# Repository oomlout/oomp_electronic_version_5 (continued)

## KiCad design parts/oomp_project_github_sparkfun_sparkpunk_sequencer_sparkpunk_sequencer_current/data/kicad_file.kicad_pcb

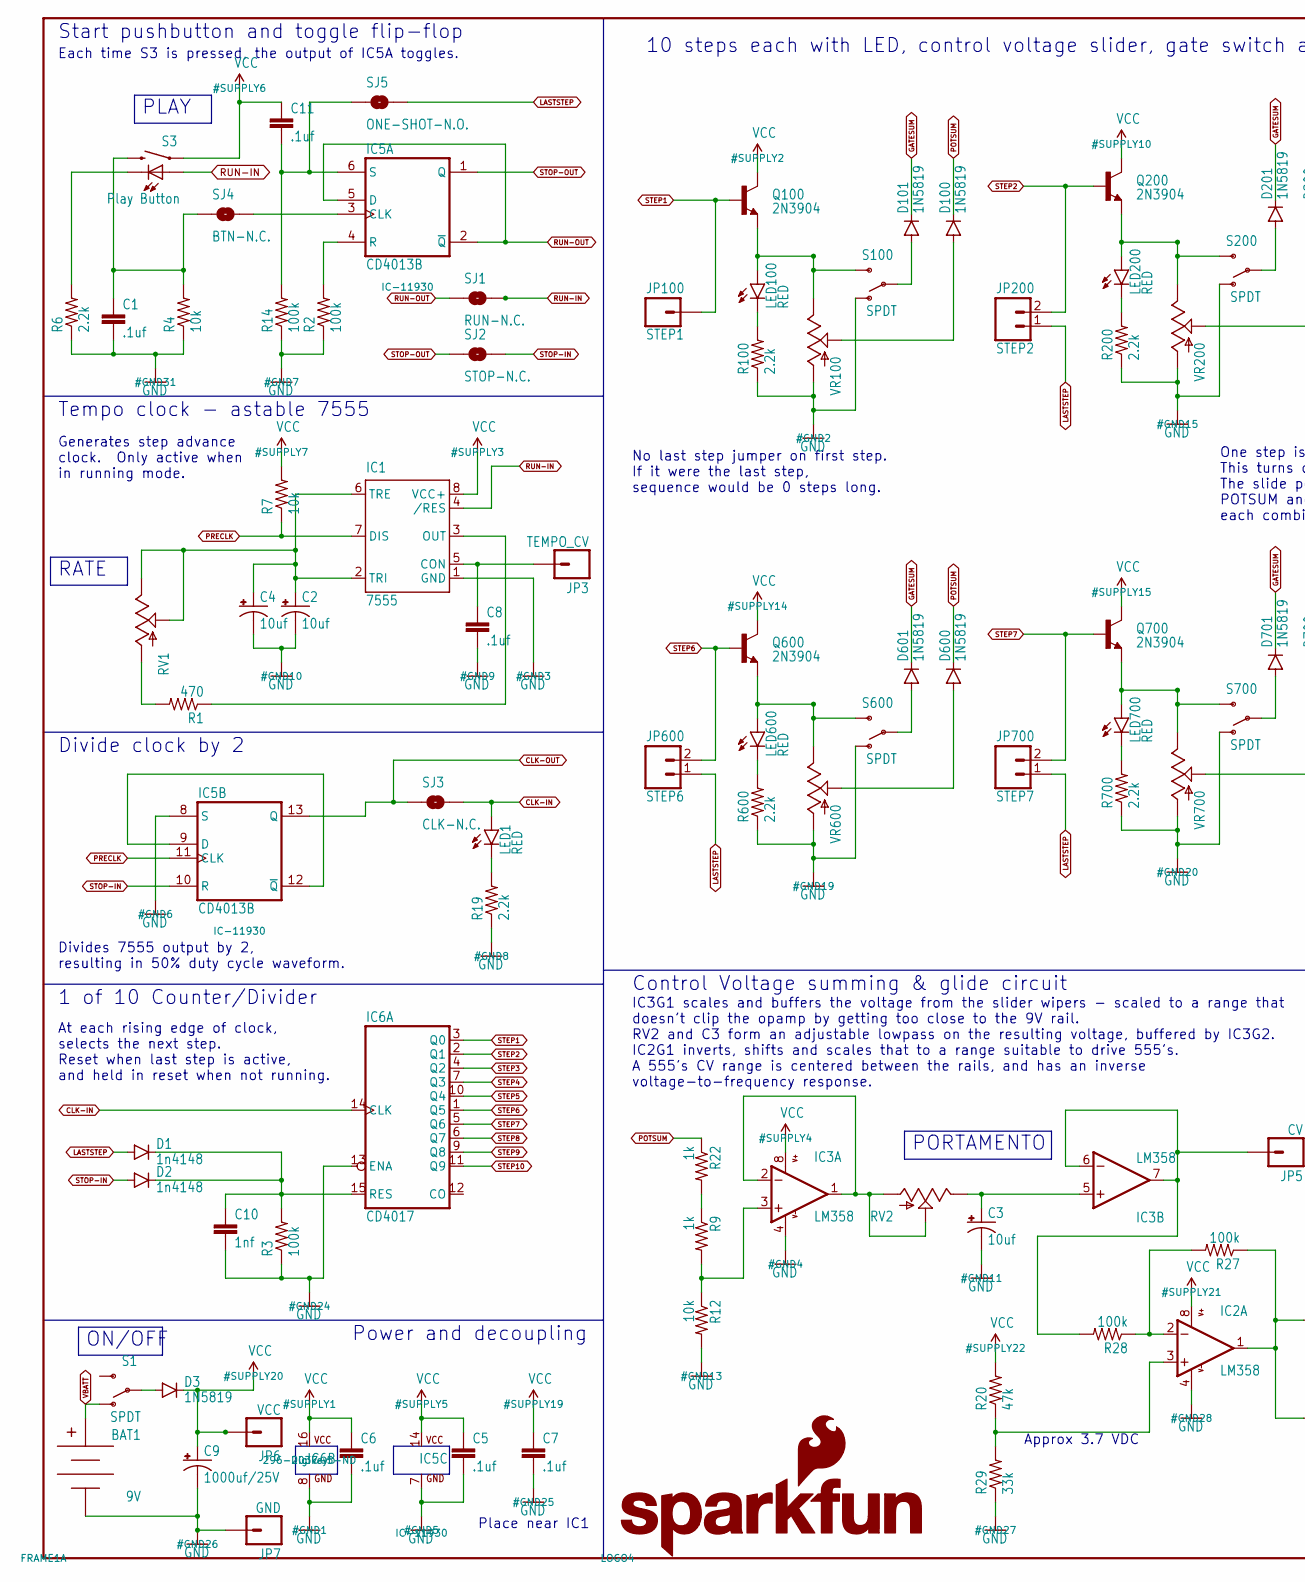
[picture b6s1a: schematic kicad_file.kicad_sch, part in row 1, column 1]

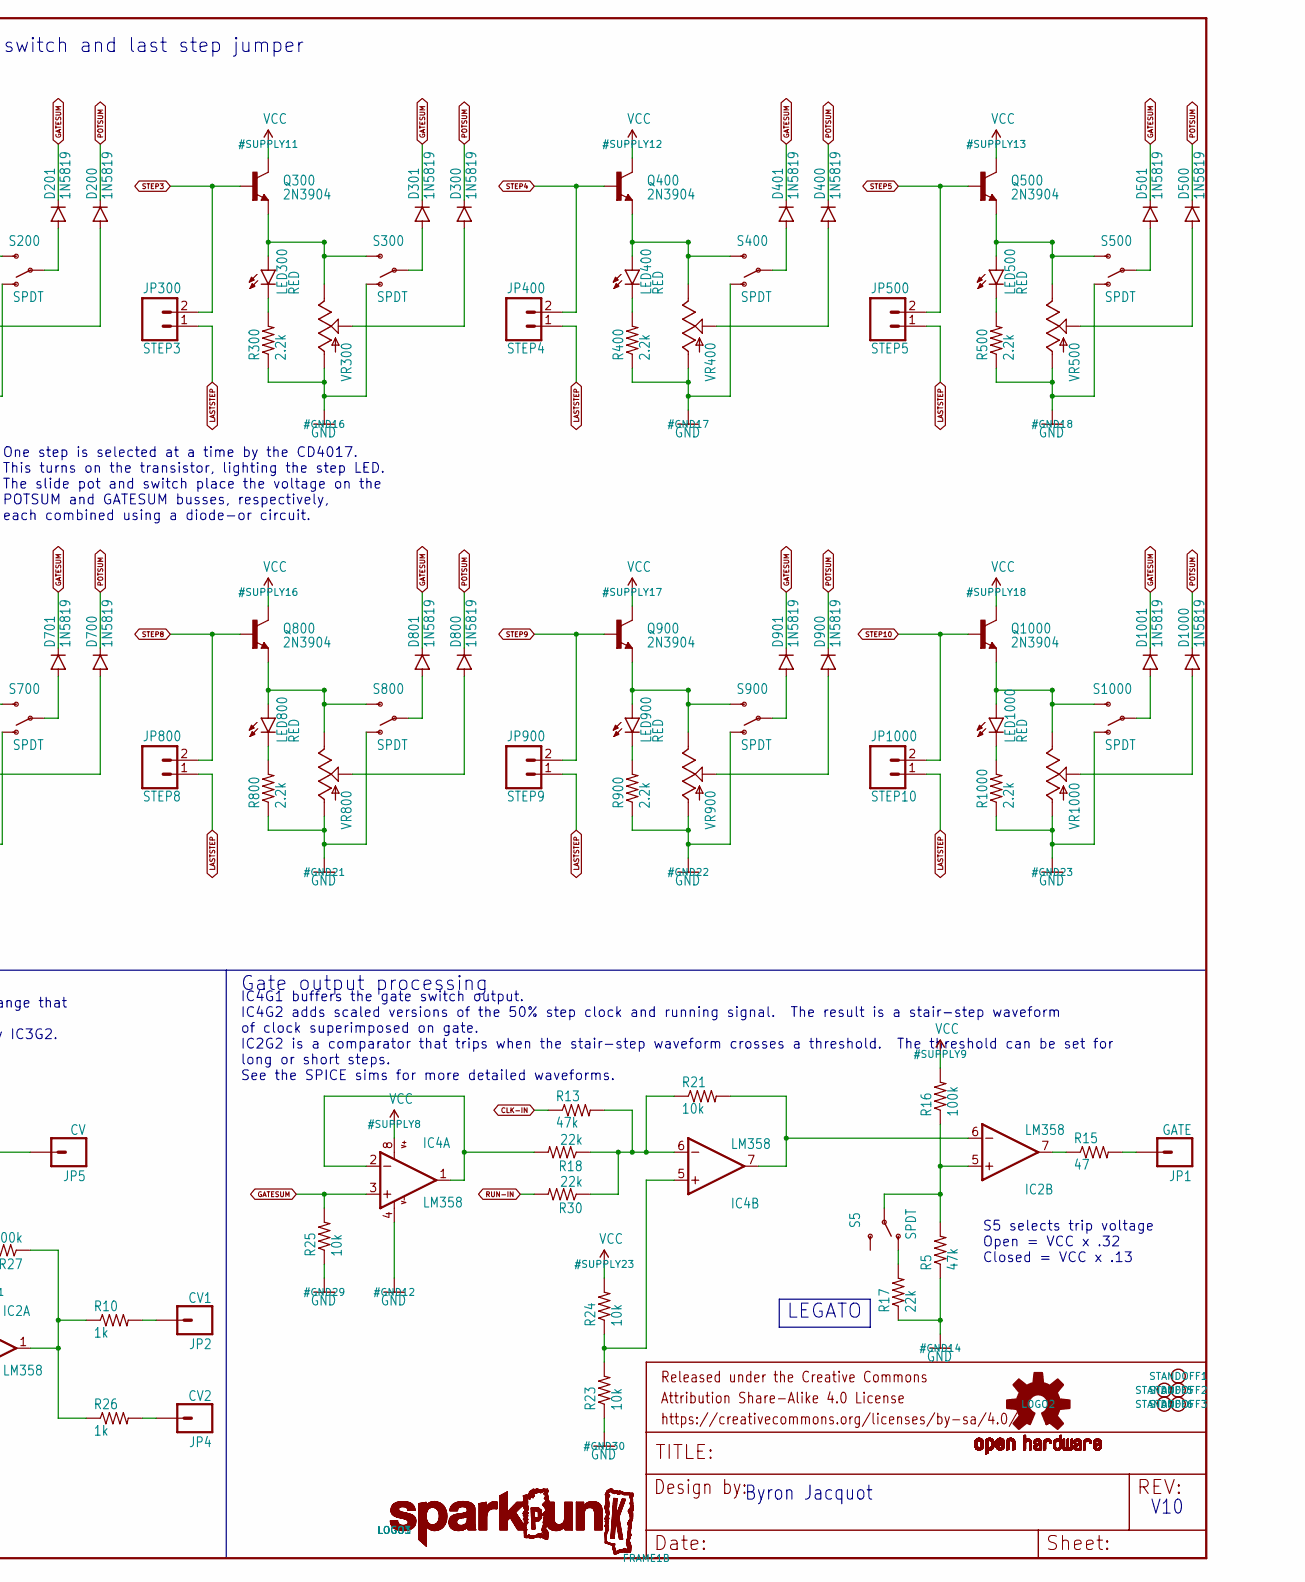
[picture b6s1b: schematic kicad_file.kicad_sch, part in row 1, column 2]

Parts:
BAT1: 9V; BC9VPC_KIT
C1, C5, C6, C7, C8, C11: .1uf; CAP-PTH-SMALL-KIT
C2, C3, C4: 10uf; CPOL-RADIAL-10UF-25V-KIT
C9: 1000uf/25V; CPOL-RADIAL-1000UF-25V-KIT
C10: 1nf; CAP-PTH-SMALL-KIT
D1, D2: 1n4148; DIODE-1N4148-KIT
D3, D100, D101, D200, D201, D300, D301, D400, D401, D500, D501, D600, D601, D700, D701, D800, D801, D900, D901, D1000, D1001: 1N5819; DIODE-1N4001-KIT
FRAME1: FRAME-LEDGER; CREATIVE_COMMONS
IC1: 7555; DIP08-KIT
IC2, IC3, IC4: LM358; DIP08-KIT
IC5: CD4013B; DIL14-KIT
IC6: CD4017; DIL16-KIT
JP1: GATE; 1X01NS
JP2: CV1; 1X01NS
JP3: TEMPO_CV; 1X01NS
JP4: CV2; 1X01NS
JP5: CV; 1X01NS
JP6: VCC; 1X01NS
JP7: GND; 1X01NS
JP100: STEP1; 1X01NS
JP200: STEP2; 1X02_NO_SILK
JP300: STEP3; 1X02_NO_SILK
JP400: STEP4; 1X02_NO_SILK
JP500: STEP5; 1X02_NO_SILK
JP600: STEP6; 1X02_NO_SILK
JP700: STEP7; 1X02_NO_SILK
JP800: STEP8; 1X02_NO_SILK
JP900: STEP9; 1X02_NO_SILK
JP1000: STEP10; 1X02_NO_SILK
LED1, LED100, LED200, LED300, LED400, LED500, LED600, LED700, LED800, LED900, LED1000: RED; LED5MM-KIT
LOGO1: SPARKPUNK_LOGO.2_INCH_TALL; SPARKPUNK_LOGO_.2
LOGO2: OSHW-LOGOM; OSHW-LOGO-M
LOGO3: SPARKPUNK_LOGO.1INCH_TALL; SPARKPUNK_LOGO_.1
LOGO4: SFE_LOGO_NAME_FLAME.4_INCH; SFE_LOGO_NAME_FLAME_.4
Q100, Q200, Q300, Q400, Q500, Q600, Q700, Q800, Q900, Q1000: 2N3904; TO-92-AMMO
R1: 470; AXIAL-0.3EZ
R2, R3, R14, R16, R27, R28: 100k; AXIAL-0.3EZ
R4, R7, R12, R21, R23, R24, R25: 10k; AXIAL-0.3EZ
R5, R13, R20: 47k; AXIAL-0.3EZ
R6, R19, R100, R200, R300, R400, R500, R600, R700, R800, R900, R1000: 2.2k; AXIAL-0.3EZ
R9, R10, R22, R26: 1k; AXIAL-0.3EZ
R15: 47; AXIAL-0.3EZ
R17, R18, R30: 22k; AXIAL-0.3EZ
R29: 33k; AXIAL-0.3EZ
RV1, RV2: 10k; ALPS_POT_KIT
S1, S5, S100, S200, S300, S400, S500, S600, S700, S800, S900, S1000: SPDT; SWITCH-SPDT_KIT
S3: Play Button; TACTILE-PTH-LED-12MM-EZ
SJ1: RUN-N.C.; SJ_2S-TRACE-PTH
SJ2: STOP-N.C.; SJ_2S-TRACE-PTH
SJ3: CLK-N.C.; SJ_2S-TRACE-PTH
SJ4: BTN-N.C.; SJ_2S-TRACE-PTH
SJ5: ONE-SHOT-N.O.; SJ_2S-PTH
STANDOFF1, STANDOFF2, STANDOFF3, STANDOFF5, STANDOFF6: STAND-OFF
VR100, VR200, VR300, VR400, VR500, VR600, VR700, VR800, VR900, VR1000: 10K; SLIDER-MEDIUM-KIT

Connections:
555OUT: IC1.3 (OUT), R1.P$1 (1)
BTN-OUT: C1.1, R4.P$2 (2), S3.2, SJ4.1
CLK-IN: IC6.14 (CLK), LED1.A, R13.P$1 (1), SJ3.2
CLK-OUT: IC5.13 (Q), SJ3.1
GATESUM: D101.C, D201.C, D301.C, D401.C, D501.C, D601.C, D701.C, D801.C, D901.C, D1001.C, IC4.3 (+IN), R25.P$2 (2)
GND: BAT1.V-, C1.2, C2.2 (-), C3.2 (-), C4.2 (-), C5.2, C6.2, C7.2, C8.2, C9.-, C10.2, IC1.1 (GND), IC2.4 (V-), IC3.4 (V-), IC4.4 (V-), IC5.7 (GND), IC5.8 (S), IC6.8 (GND), IC6.13 (ENA), JP7.1, R2.P$1 (1), R3.P$1 (1), R4.P$1 (1), R5.P$1 (1), R6.P$1 (1), R12.P$2 (2), R14.P$1 (1), R17.P$1 (1), R19.P$1 (1), R23.P$1 (1), R25.P$1 (1), R29.P$1 (1), R100.P$1 (1), R200.P$1 (1), R300.P$1 (1), R400.P$1 (1), R500.P$1 (1), R600.P$1 (1), R700.P$1 (1), R800.P$1 (1), R900.P$1 (1), R1000.P$1 (1), S100.1 (O), S200.1 (O), S300.1 (O), S400.1 (O), S500.1 (O), S600.1 (O), S700.1 (O), S800.1 (O), S900.1 (O), S1000.1 (O), VR100.BOTTOM (A), VR200.BOTTOM (A), VR300.BOTTOM (A), VR400.BOTTOM (A), VR500.BOTTOM (A), VR600.BOTTOM (A), VR700.BOTTOM (A), VR800.BOTTOM (A), VR900.BOTTOM (A), VR1000.BOTTOM (A)
LASTSTEP: D1.A, JP200.1, JP300.1, JP400.1, JP500.1, JP600.1, JP700.1, JP800.1, JP900.1, JP1000.1, SJ5.2
unnamed: LED100.A, Q100.1 (E), S100.3 (S), VR100.TOP (E)
unnamed: LED100.K (C), R100.P$2 (2)
unnamed: D101.A, S100.2
unnamed: D100.A, VR100.WIPER (S)
unnamed: R1.P$2 (2), RV1.P$3 (A)
unnamed: IC3.1 (OUT), IC3.2 (-IN), RV2.P$2 (S), RV2.P$3 (A)
unnamed: C8.1, IC1.5 (CON), JP3.1
unnamed: R6.P$2 (2), S3.C
unnamed: IC5.4 (R), R2.P$2 (2)
unnamed: C2.1 (+), C4.1 (+), IC1.2 (TRI), IC1.6 (TRE), RV1.P$1 (E), RV1.P$2 (S)
unnamed: IC4.1 (OUT), IC4.2 (-IN), R18.P$2 (2)
unnamed: LED1.K (C), R19.P$2 (2)
unnamed: C10.1, D1.C, D2.C, IC6.15 (RES), R3.P$2 (2)
unnamed: IC3.3 (+IN), R9.P$2 (2), R12.P$1 (1)
unnamed: R9.P$1 (1), R22.P$2 (2)
unnamed: IC2.2 (-IN), R27.P$2 (2), R28.P$1 (1)
unnamed: C3.1 (+), IC3.5 (+IN), RV2.P$1 (E)
unnamed: IC2.3 (+IN), R20.P$1 (1), R29.P$2 (2)
unnamed: JP1.1, R15.P$2 (2)
unnamed: IC5.3 (CLK), SJ4.2
unnamed: IC2.5 (+IN), R5.P$2 (2), R16.P$1 (1), S5.2
unnamed: IC2.7 (OUT), R15.P$1 (1)
unnamed: R17.P$2 (2), S5.1 (O)
unnamed: IC5.9 (D), IC5.12 (~Q)
unnamed: LED200.A, Q200.1 (E), S200.3 (S), VR200.TOP (E)
unnamed: LED200.K (C), R200.P$2 (2)
unnamed: D200.A, VR200.WIPER (S)
unnamed: D201.A, S200.2
unnamed: LED300.A, Q300.1 (E), S300.3 (S), VR300.TOP (E)
unnamed: LED300.K (C), R300.P$2 (2)
unnamed: D300.A, VR300.WIPER (S)
unnamed: D301.A, S300.2
unnamed: LED400.A, Q400.1 (E), S400.3 (S), VR400.TOP (E)
unnamed: LED400.K (C), R400.P$2 (2)
unnamed: D400.A, VR400.WIPER (S)
unnamed: D401.A, S400.2
unnamed: LED500.A, Q500.1 (E), S500.3 (S), VR500.TOP (E)
unnamed: LED500.K (C), R500.P$2 (2)
unnamed: D500.A, VR500.WIPER (S)
unnamed: D501.A, S500.2
unnamed: LED600.A, Q600.1 (E), S600.3 (S), VR600.TOP (E)
unnamed: LED600.K (C), R600.P$2 (2)
unnamed: D600.A, VR600.WIPER (S)
unnamed: D601.A, S600.2
unnamed: LED700.A, Q700.1 (E), S700.3 (S), VR700.TOP (E)
unnamed: LED700.K (C), R700.P$2 (2)
unnamed: D700.A, VR700.WIPER (S)
unnamed: D701.A, S700.2
unnamed: LED800.A, Q800.1 (E), S800.3 (S), VR800.TOP (E)
unnamed: LED800.K (C), R800.P$2 (2)
unnamed: D800.A, VR800.WIPER (S)
unnamed: D801.A, S800.2
unnamed: LED900.A, Q900.1 (E), S900.3 (S), VR900.TOP (E)
unnamed: LED900.K (C), R900.P$2 (2)
unnamed: D900.A, VR900.WIPER (S)
unnamed: D901.A, S900.2
unnamed: LED1000.A, Q1000.1 (E), S1000.3 (S), VR1000.TOP (E)
unnamed: LED1000.K (C), R1000.P$2 (2)
unnamed: D1000.A, VR1000.WIPER (S)
unnamed: D1001.A, S1000.2
unnamed: C11.2, IC5.6 (S), R14.P$2 (2), SJ5.1
unnamed: IC4.6 (-IN), R13.P$2 (2), R18.P$1 (1), R21.P$1 (1), R30.P$1 (1)
unnamed: IC3.6 (-IN), IC3.7 (OUT), JP5.1, R28.P$2 (2)
unnamed: IC2.1 (OUT), R10.P$1 (1), R26.P$1 (1), R27.P$1 (1)
unnamed: JP4.1, R26.P$2 (2)
unnamed: JP2.1, R10.P$2 (2)
unnamed: IC2.6 (-IN), IC4.7 (OUT), R21.P$2 (2)
unnamed: IC4.5 (+IN), R23.P$2 (2), R24.P$1 (1)
unnamed: D3.A, S1.2
POTSUM: D100.C, D200.C, D300.C, D400.C, D500.C, D600.C, D700.C, D800.C, D900.C, D1000.C, R22.P$1 (1)
PRECLK: IC1.7 (DIS), IC5.11 (CLK), R7.P$1 (1)
RUN-IN: IC1.4 (/RES), R30.P$2 (2), S3.A, SJ1.2
RUN-OUT: IC5.2 (~Q), IC5.5 (D), SJ1.1
STEP1: IC6.3 (Q0), JP100.1, Q100.2 (B)
STEP2: IC6.2 (Q1), JP200.2, Q200.2 (B)
STEP3: IC6.4 (Q2), JP300.2, Q300.2 (B)
STEP4: IC6.7 (Q3), JP400.2, Q400.2 (B)
STEP5: IC6.10 (Q4), JP500.2, Q500.2 (B)
STEP6: IC6.1 (Q5), JP600.2, Q600.2 (B)
STEP7: IC6.5 (Q6), JP700.2, Q700.2 (B)
STEP8: IC6.6 (Q7), JP800.2, Q800.2 (B)
STEP9: IC6.9 (Q8), JP900.2, Q900.2 (B)
STEP10: IC6.11 (Q9), JP1000.2, Q1000.2 (B)
STOP-IN: D2.A, IC5.10 (R), SJ2.2
STOP-OUT: IC5.1 (Q), SJ2.1
VBATT: BAT1.V+, S1.1 (O)
VCC: C5.1, C6.1, C7.1, C9.+, C11.1, D3.C, IC1.8 (VCC+), IC2.8 (V+), IC3.8 (V+), IC4.8 (V+), IC5.14 (VCC), IC6.16 (VCC), JP6.1, Q100.3 (C), Q200.3 (C), Q300.3 (C), Q400.3 (C), Q500.3 (C), Q600.3 (C), Q700.3 (C), Q800.3 (C), Q900.3 (C), Q1000.3 (C), R7.P$2 (2), R16.P$2 (2), R20.P$2 (2), R24.P$2 (2), S3.4 (1)

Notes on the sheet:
Each time S3 is pressed, the output of IC5A toggles.
Start pushbutton and toggle flip-flop
Power and decoupling
10 steps each with LED, control voltage slider, gate switch and last step jumper
No last step jumper on first step. If it were the last step, sequence would be 0 steps long.
S5 selects trip voltage Open = VCC x .32 Closed = VCC x .13
Byron Jacquot
Place near IC1
At each rising edge of clock, selects the next step. Reset when last step is active, and held in reset when not running.
Divide clock by 2
Generates step advance clock. Only active when in running mode.
PORTAMENTO
ON/OFF
V10
Approx 3.7 VDC
Gate output processing
RATE
IC4G1 buffers the gate switch output. IC4G2 adds scaled versions of the 50% step clock and running signal. The result is a stair-step waveform of clock superimposed on gate. IC2G2 is a comparator that trips when the stair-step waveform crosses a threshold. The threshold can be set for long or short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
IC3G1 scales and buffers the voltage from the slider wipers - scaled to a range that doesn't clip the opamp by getting too close to the 9V rail. RV2 and C3 form an adjustable lowpass on the resulting voltage, buffered by IC3G2. IC2G1 inverts, shifts and scales that to a range suitable to drive 555'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
Control Voltage summing & glide circuit
PLAY
Divides 7555 output by 2, resulting in 50% duty cycle waveform.
1 of 10 Counter/Divider
One step is selected at a time by the CD4017. This turns on the transistor, lighting the step LED. The slide pot and switch place the voltage on the POTSUM and GATESUM busses, respectively, each combined using a diode-or circuit.
Tempo clock - astable 7555
LEGATO

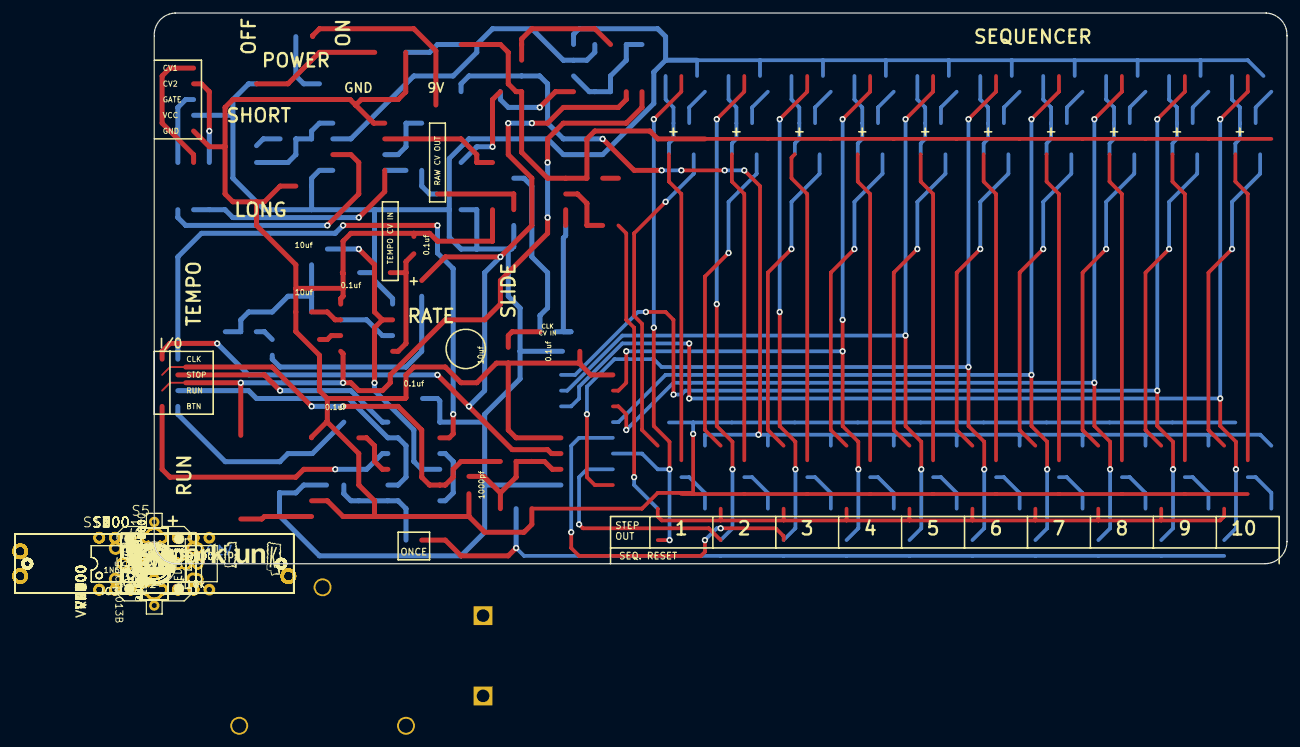
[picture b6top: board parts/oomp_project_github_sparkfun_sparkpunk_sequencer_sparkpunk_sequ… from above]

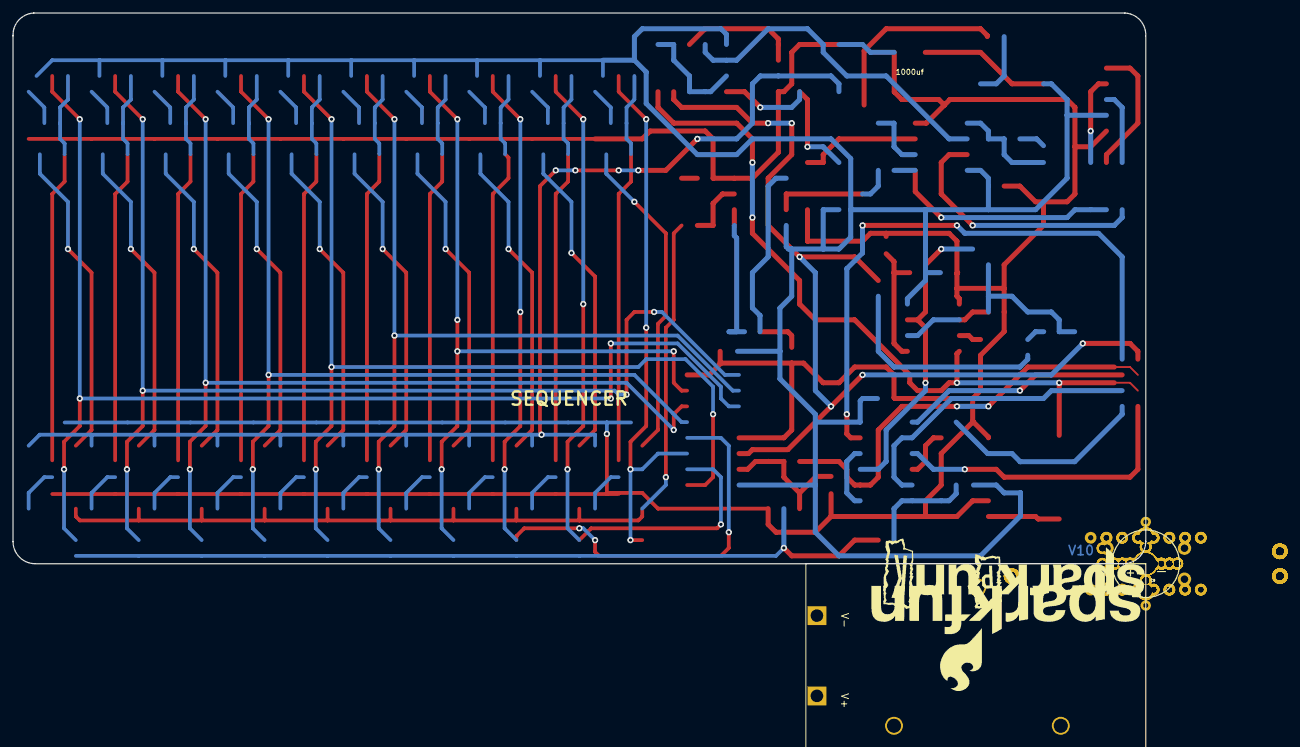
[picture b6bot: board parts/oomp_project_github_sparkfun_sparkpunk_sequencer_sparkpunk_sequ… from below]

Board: 2 copper layers, 182.9 x 88.9 mm, 157 parts (4 on the bottom side), 94 nets.

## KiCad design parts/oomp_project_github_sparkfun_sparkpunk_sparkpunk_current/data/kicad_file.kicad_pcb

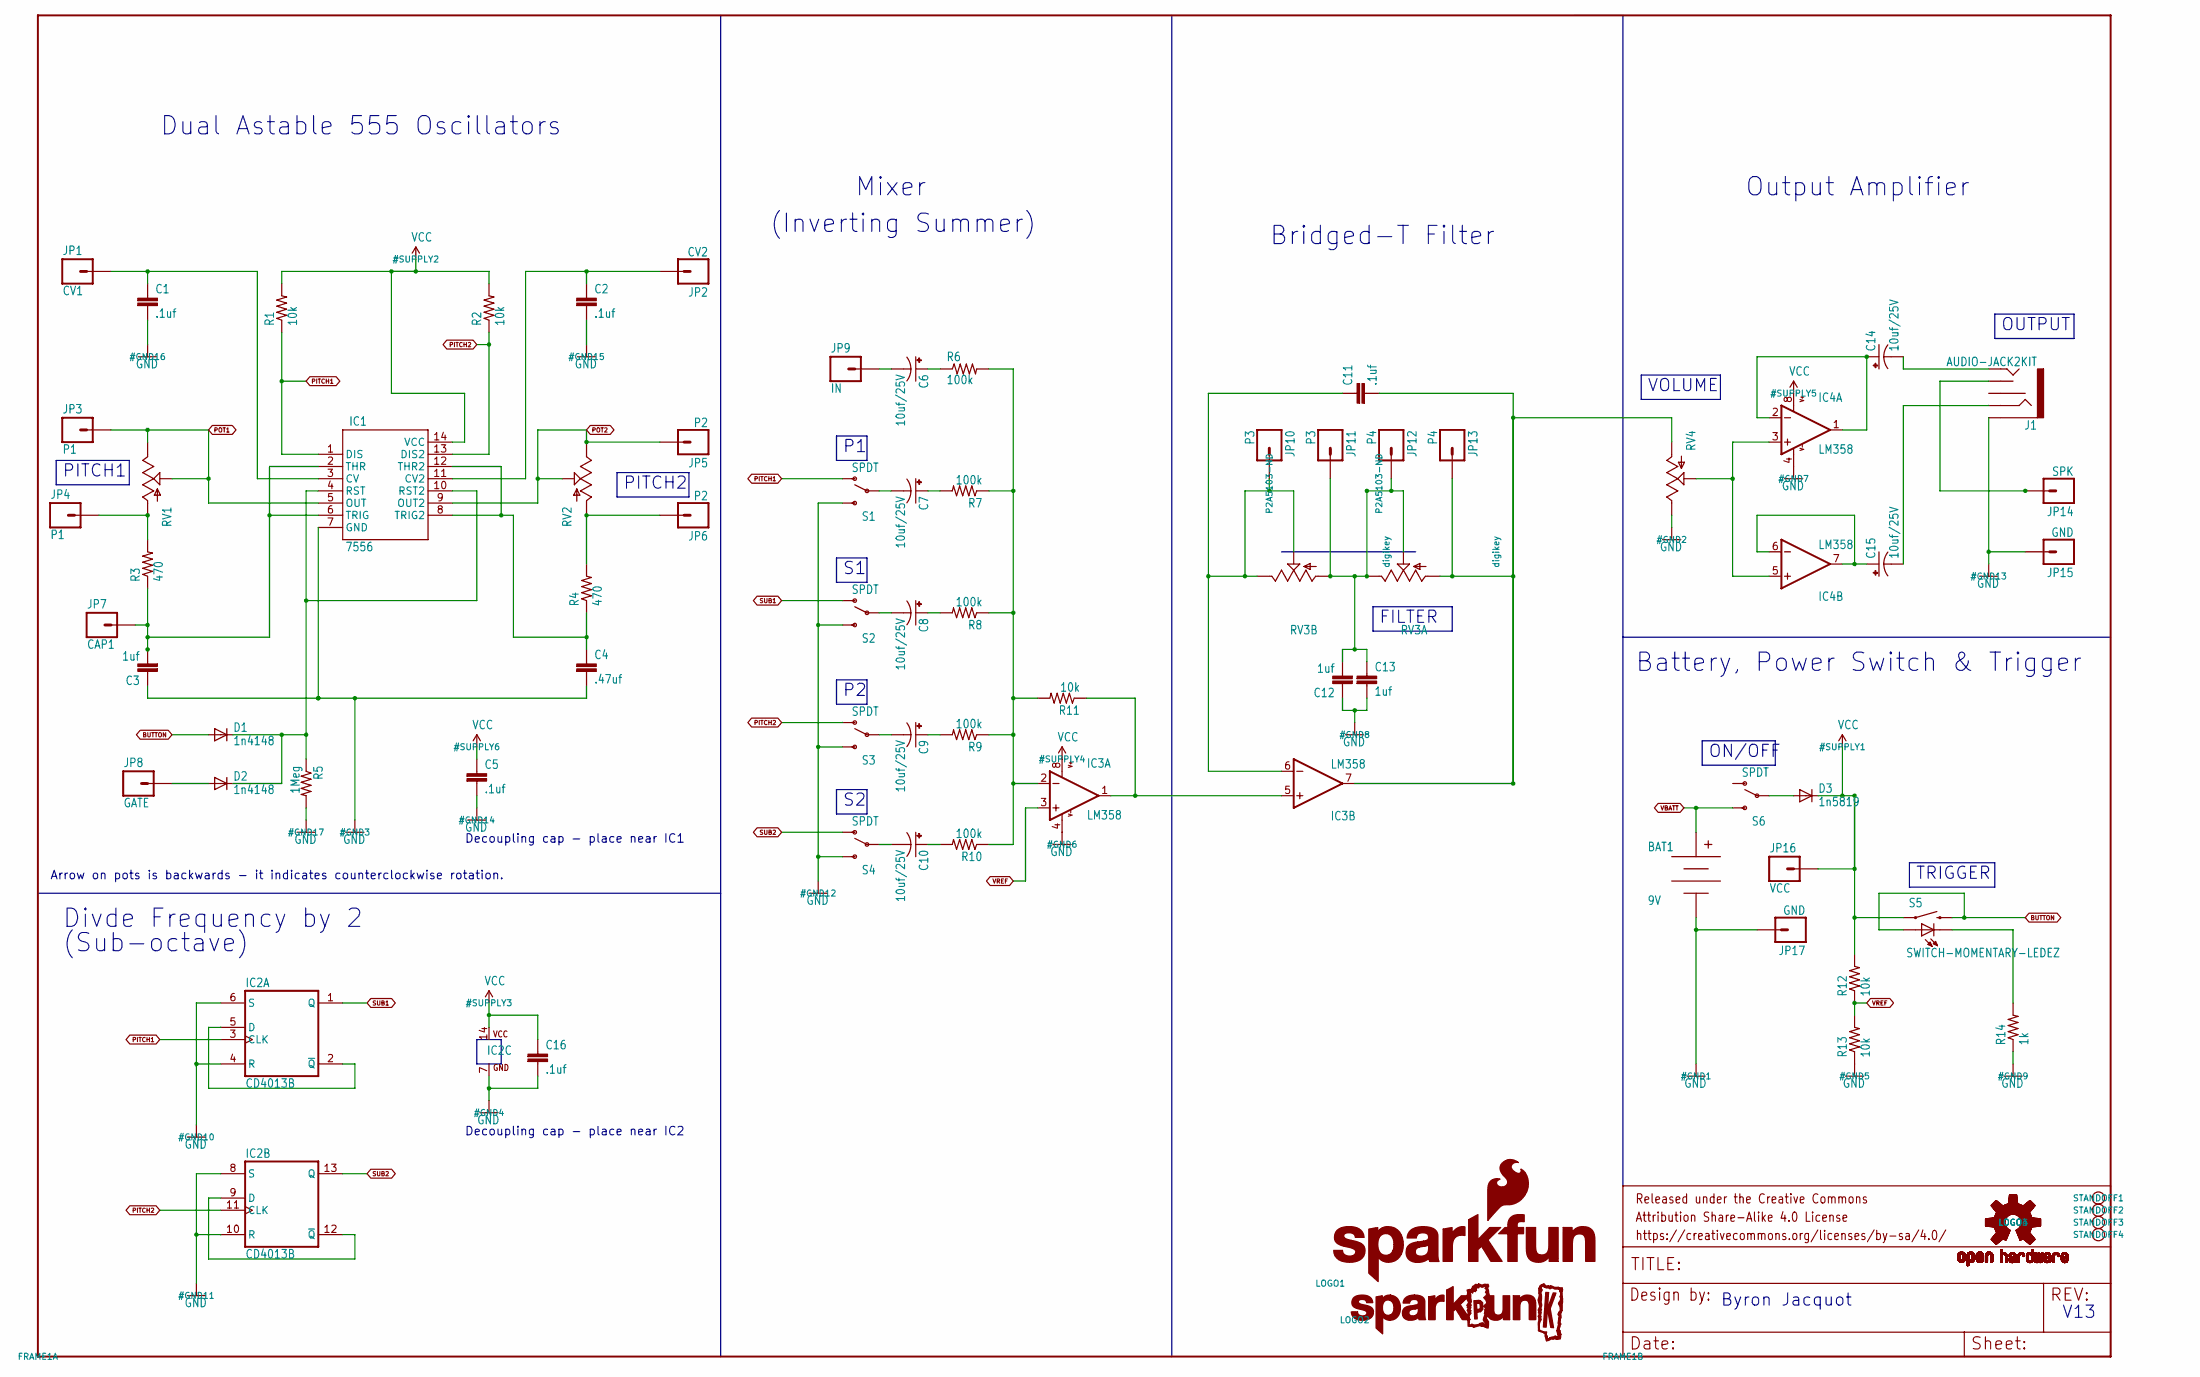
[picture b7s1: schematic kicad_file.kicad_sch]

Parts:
BAT1: 9V; BC9VPC_KIT
C1, C2, C5, C11, C16: .1uf; CAP-PTH-SMALL-KIT
C3, C12, C13: 1uf; CAP-PTH-SMALL-KIT
C4: .47uf; CAP-PTH-SMALL-KIT
C6, C7, C8, C9, C10, C14, C15: 10uf/25V; CPOL-RADIAL-10UF-25V-KIT
D1, D2: 1n4148; DIODE-1N4148-KIT
D3: 1n5819; DIODE-1N4001-KIT
FRAME1: FRAME-LEDGER; CREATIVE_COMMONS
IC1: 7556; DIL14-KIT
IC2: CD4013B; DIL14-KIT
IC3, IC4: LM358; DIP08-KIT
J1: AUDIO-JACK2KIT; AUDIO-JACK-KIT
JP1: CV1; 1X01NS
JP2: CV2; 1X01NS
JP3, JP4: P1; 1X01NS
JP5, JP6: P2; 1X01NS
JP7: CAP1; 1X01NS
JP8: GATE; 1X01NS
JP9: IN; 1X01NS
JP10, JP11: P3; 1X01NS
JP12, JP13: P4; 1X01NS
JP14: SPK; 1X01NS
JP15, JP17: GND; 1X01NS
JP16: VCC; 1X01NS
LOGO1: SFE_LOGO_NAME_FLAME.2_INCH; SFE_LOGO_NAME_FLAME_.2
LOGO2: SPARKPUNK_LOGO.1INCH_TALL; SPARKPUNK_LOGO_.1
LOGO3, LOGO4: OSHW-LOGOM; OSHW-LOGO-M
R1, R2, R11, R12, R13: 10k; AXIAL-0.3EZ
R3, R4: 470; AXIAL-0.3EZ
R5: 1Meg; AXIAL-0.3EZ
R6, R7, R8, R9, R10: 100k; AXIAL-0.3EZ
R14: 1k; AXIAL-0.3EZ
RV1, RV2, RV4: 10k; ALPS_POT_KIT
RV3: 10k; POT_PANASONIC_DUAL_VERT_KIT
S1, S2, S3, S4, S6: SPDT; SWITCH-SPDT_KIT
S5: SWITCH-MOMENTARY-LEDEZ; TACTILE-PTH-LED-12MM-EZ
STANDOFF1, STANDOFF2, STANDOFF3, STANDOFF4: STAND-OFF

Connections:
BUTTON: D1.A, S5.2, S5.A
FILT-OUT: C11.2, IC3.7 (OUT), JP13.1, RV3.A3 (A), RV4.P$3 (A)
GND: BAT1.V-, C1.2, C2.2, C3.1, C4.2, C5.2, C12.1, C13.2, C16.2, IC1.7 (GND), IC2.4 (R), IC2.6 (S), IC2.7 (GND), IC2.8 (S), IC2.10 (R), IC3.4 (V-), IC4.4 (V-), J1.SLEEVE, JP15.1, JP17.1, R5.P$2 (2), R13.P$1 (1), R14.P$1 (1), RV4.P$1 (E), S1.3 (S), S2.3 (S), S3.3 (S), S4.3 (S)
N: IC4.3 (+IN), IC4.5 (+IN), RV4.P$2 (S)
unnamed: D2.A, JP8.1
unnamed: C4.1, IC1.8 (TRIG2), IC1.12 (THR2), R4.P$1 (1)
unnamed: D1.C, D2.C, IC1.4 (RST), IC1.10 (RST2), R5.P$1 (1)
unnamed: D3.A, S6.2
unnamed: JP6.1, R4.P$2 (2), RV2.P$3 (A)
unnamed: R14.P$2 (2), S5.C
unnamed: IC2.2 (~Q), IC2.5 (D)
unnamed: IC2.9 (D), IC2.12 (~Q)
unnamed: JP4.1, R3.P$2 (2), RV1.P$3 (A)
unnamed: C10.2 (-), S4.2
unnamed: J1.TSH, JP14.1
unnamed: C14.1 (+), IC4.1 (OUT), IC4.2 (-IN)
unnamed: C15.2 (-), J1.RING
unnamed: C10.1 (+), R10.P$2 (2)
unnamed: C9.1 (+), R9.P$2 (2)
unnamed: C9.2 (-), S3.2
unnamed: C6.2 (-), JP9.1
unnamed: C6.1 (+), R6.P$1 (1)
unnamed: C7.2 (-), S1.2
unnamed: C8.2 (-), S2.2
unnamed: C15.1 (+), IC4.6 (-IN), IC4.7 (OUT)
unnamed: IC3.2 (-IN), R6.P$2 (2), R7.P$1 (1), R8.P$1 (1), R9.P$1 (1), R10.P$1 (1), R11.P$2 (2)
unnamed: IC3.1 (OUT), IC3.5 (+IN), R11.P$1 (1)
unnamed: C8.1 (+), R8.P$2 (2)
unnamed: C7.1 (+), R7.P$2 (2)
unnamed: C14.2 (-), J1.TIP
unnamed: C11.1, IC3.6 (-IN), JP10.1, RV3.B1 (E), RV3.B2 (S)
unnamed: C12.2, C13.1, JP11.1, JP12.1, RV3.A1 (E), RV3.A2 (S), RV3.B3 (A)
PITCH1: IC1.1 (DIS), IC2.3 (CLK), R1.P$1 (1), S1.1 (O)
PITCH2: IC1.13 (DIS2), IC2.11 (CLK), R2.P$1 (1), S3.1 (O)
POT1: IC1.5 (OUT), JP3.1, RV1.P$1 (E), RV1.P$2 (S)
POT2: IC1.9 (OUT2), JP5.1, RV2.P$1 (E), RV2.P$2 (S)
SUB1: IC2.1 (Q), S2.1 (O)
SUB2: IC2.13 (Q), S4.1 (O)
VBATT: BAT1.V+, S6.3 (S)
VCAP1: C3.2, IC1.2 (THR), IC1.6 (TRIG), JP7.1, R3.P$1 (1)
VCC: C5.1, C16.1, D3.C, IC1.14 (VCC), IC2.14 (VCC), IC3.8 (V+), IC4.8 (V+), JP16.1, R1.P$2 (2), R2.P$2 (2), R12.P$2 (2), S5.4 (1)
VCC1: C2.1, IC1.11 (CV2), JP2.1
VCC2: C1.1, IC1.3 (CV), JP1.1
VREF: IC3.3 (+IN), R12.P$1 (1), R13.P$2 (2)

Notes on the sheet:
VOLUME
Mixer
PITCH1
OUTPUT
(Sub-octave)
PITCH2
Byron Jacquot
TRIGGER
Divde Frequency by 2
Decoupling cap - place near IC1
Battery, Power Switch & Trigger
(Inverting Summer)
Dual Astable 555 Oscillators
FILTER
Arrow on pots is backwards - it indicates counterclockwise rotation.
Bridged-T Filter
V13
Decoupling cap - place near IC2
ON/OFF
Output Amplifier

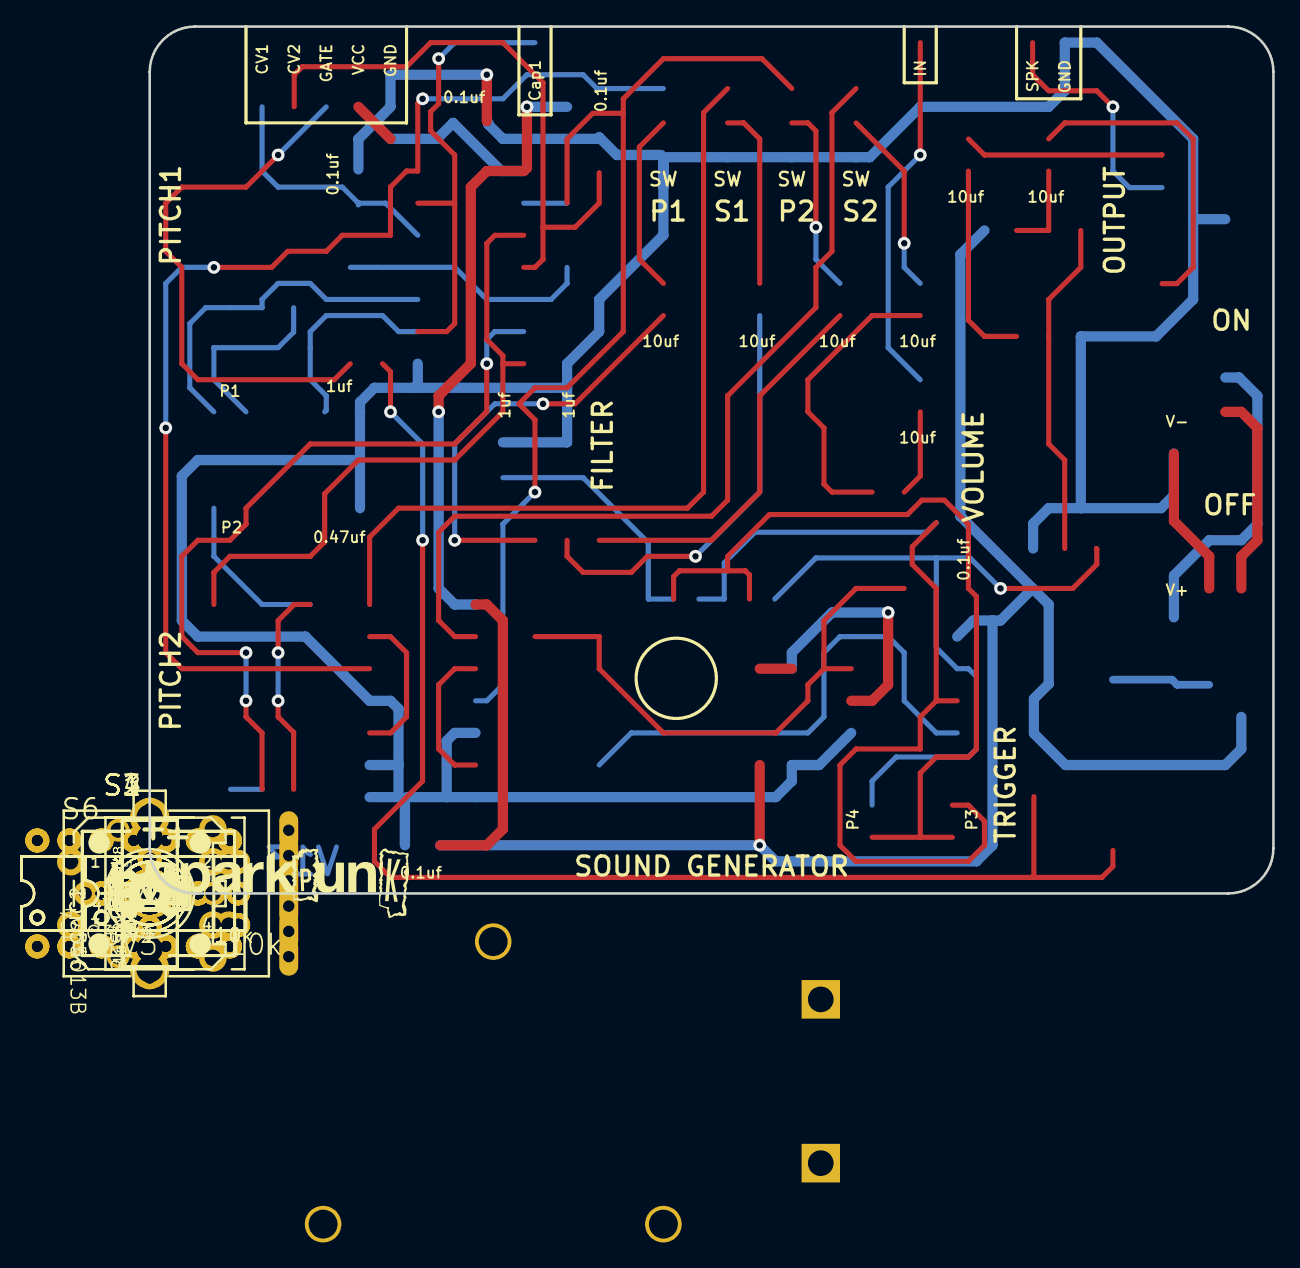
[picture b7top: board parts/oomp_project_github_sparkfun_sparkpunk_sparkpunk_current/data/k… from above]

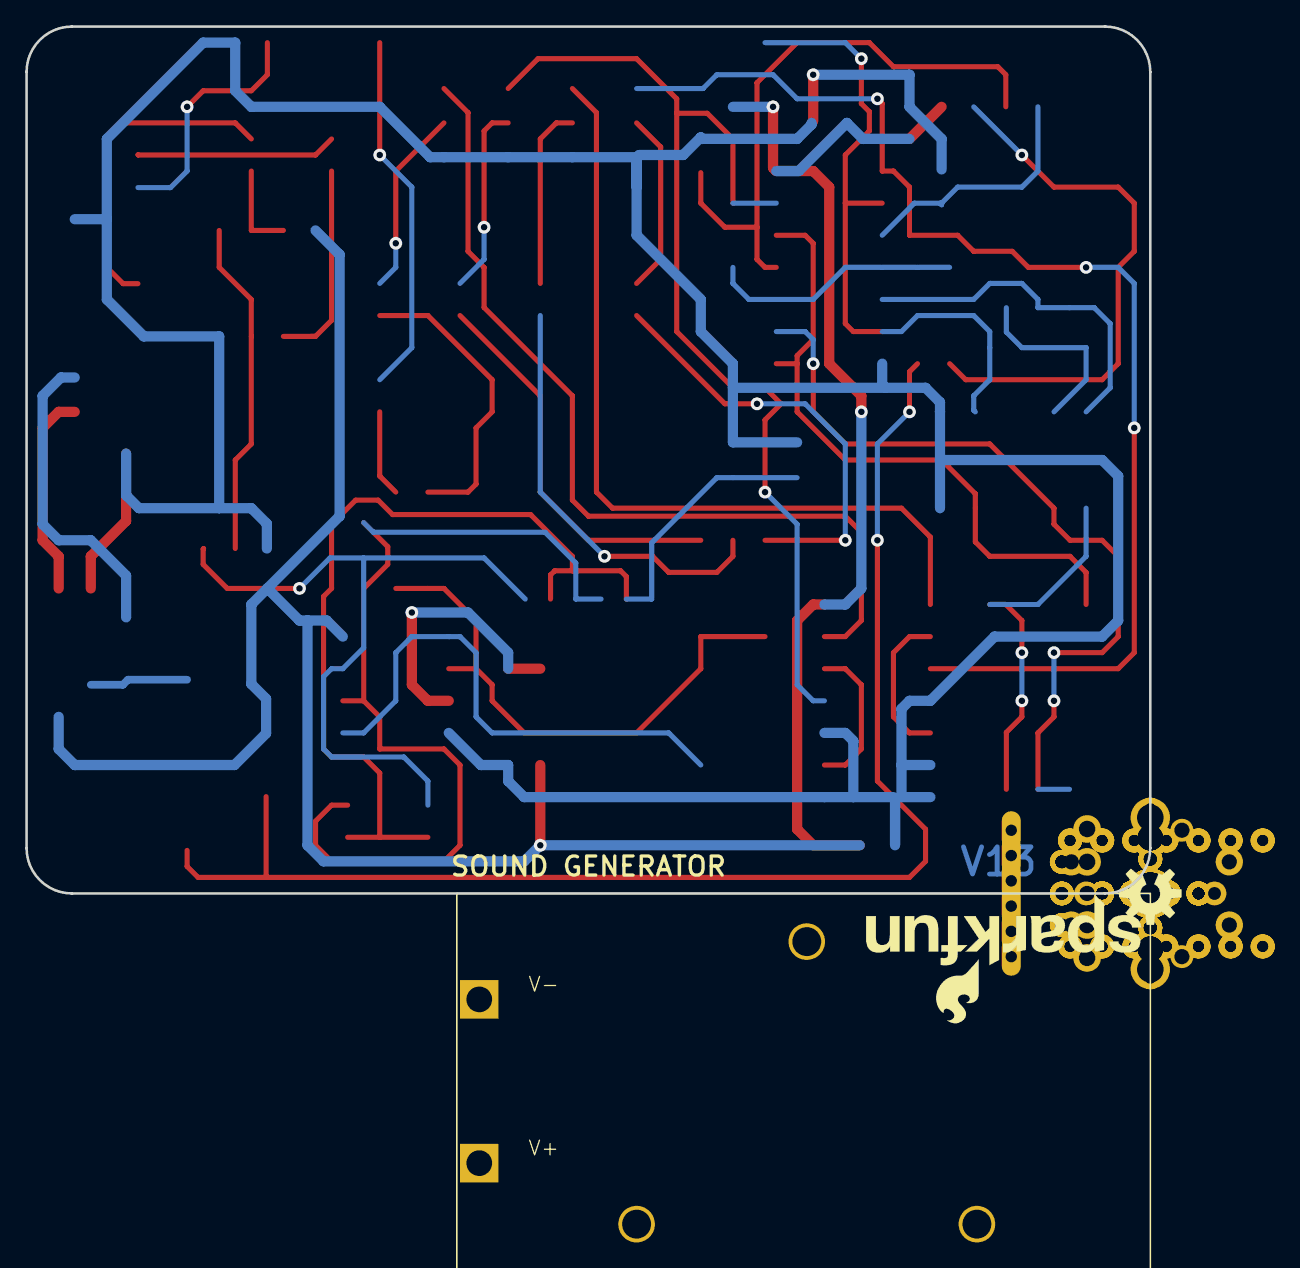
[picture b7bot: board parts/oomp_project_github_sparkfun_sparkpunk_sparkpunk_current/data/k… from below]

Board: 2 copper layers, 88.9 x 68.6 mm, 75 parts (3 on the bottom side), 44 nets.

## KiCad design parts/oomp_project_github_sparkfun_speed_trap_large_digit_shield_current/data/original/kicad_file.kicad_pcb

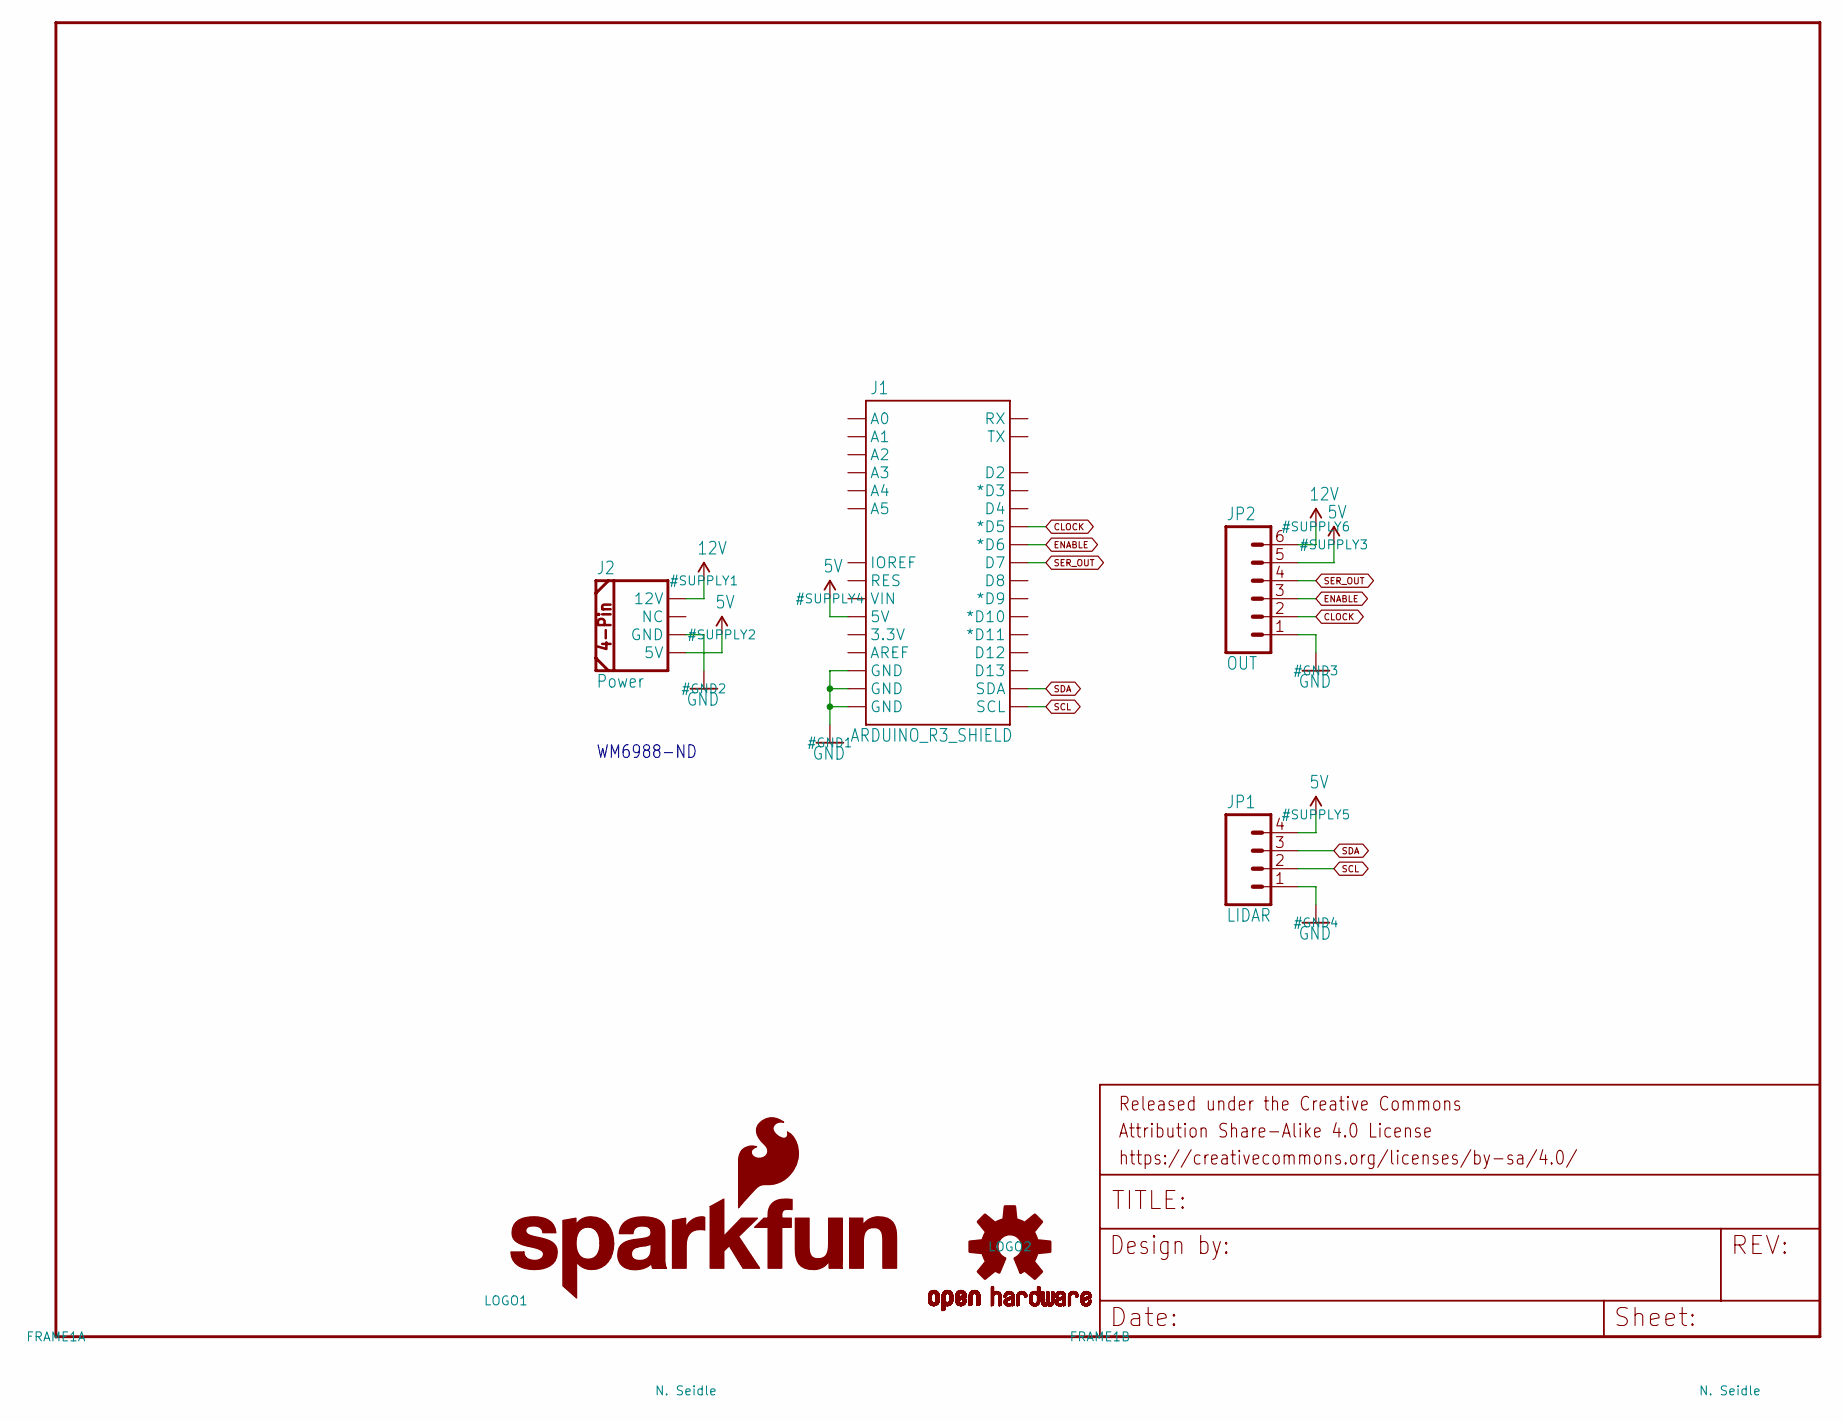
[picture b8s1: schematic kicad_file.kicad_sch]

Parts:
FRAME1: FRAME-LETTER; CREATIVE_COMMONS
J1: ARDUINO_R3_SHIELD; UNO_R3_SHIELD
J2: Power; COMPUTER-PERIPHERAL-POWER-RA
JP1: LIDAR; JST-4-PTH
JP2: OUT; 1X06
LOGO1: SFE_LOGO_NAME_FLAME.2_INCH; SFE_LOGO_NAME_FLAME_.2
LOGO2: OSHW-LOGOS; OSHW-LOGO-S

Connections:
5V: J1.5V, J2.5V, JP1.4, JP2.5
12V: J2.12V, JP2.6
CLOCK: J1.D5 (*D5), JP2.2
ENABLE: J1.D6 (*D6), JP2.3
GND: J1.GND@0 (GND), J1.GND@1 (GND), J1.GND@2 (GND), J2.GND, JP1.1, JP2.1
SCL: J1.SCL, JP1.2
SDA: J1.SDA, JP1.3
SER_OUT: J1.D7, JP2.4

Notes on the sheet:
WM6988-ND
